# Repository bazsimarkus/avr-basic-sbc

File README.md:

<h1 align="center">avr-basic-sbc</h1>

<p align="center">
  <strong>An ATmega1284P-based single board computer</strong><br>
  Composite video output &bull; PS/2 keyboard input &bull; Tiny BASIC interpreter with graphics, sound, GPIO, and serial I/O
</p>

<p align="center">
  <table align="center">
    <tr>
      <td align="center">
        
      </td>
      <td align="center">
        
      </td>
    </tr>
  </table>
</p>

---

## Table of Contents

- [Overview](#overview)
- [Features](#features)
- [Hardware](#hardware)
  - [Main Board](#main-board)
  - [Schematic](#schematic)
  - [Bill of Materials](#bill-of-materials)
  - [Pin Mapping](#pin-mapping)
- [Firmware](#firmware)
  - [Architecture](#architecture)
  - [Graphics & Video](#graphics--video)
  - [Tiny BASIC Interpreter](#tiny-basic-interpreter)
  - [Building & Flashing](#building--flashing)
- [Boomerang Shields](#boomerang-shields)
  - [Serial Boomerang Shield](#serial-boomerang-shield)
  - [Bluetooth Boomerang Shield](#bluetooth-boomerang-shield-perfboard-prototype)
  - [Seven Segment Display Extension](#seven-segment-display-extension-perfboard-prototype)
- [SBC Studio](#sbc-studio)
  - [Code Editor & Serial Upload](#code-editor--serial-upload)
  - [Bitmap Editor & Loader](#bitmap-editor--loader)
  - [MIDI to BAS Converter](#midi-to-bas-converter)
- [BASIC Examples](#basic-examples)
  - [Hello World](#hello-world)
  - [Graphics Demos](#graphics-demos)
  - [Games](#games)
  - [Sound Examples](#sound-examples)
  - [Hardware I/O Examples](#hardware-io-examples)
- [Known Limitations & Future Ideas](#known-limitations--future-ideas)
- [Personal Notes](#personal-notes)
- [Inspirations & Credits](#inspirations--credits)

---

## Overview

I always loved retrocomputing. As a kid I played around with a Commodore 64 - which I still own to this day - and I was always fascinated by the fact that computers are really just embedded systems, just nowadays unimaginably fast ones. This project grew out of that fascination.

The idea is not completely original. Many people have built similar things, and my two biggest inspirations were Jörg Wolfram's [AVR ChipBASIC](https://www.jcwolfram.de/projekte/avr/chipbasic/main.php) and Juan J. Martínez's [DAN64](https://www.usebox.net/jjm/dan64/). Neither was quite what I had in mind though - I wanted something simple to use, simple to develop for, and simple to build. A Tiny BASIC based single board computer with composite video output, a PS/2 keyboard, and some GPIO, all on a single through-hole PCB. So I decided to build my own, and here it is.

The **AVR-SBC** is an ATmega1284P-based single board computer running a Tiny BASIC interpreter. It generates a composite video signal (320×240, PAL) directly from the microcontroller, accepts input from a PS/2 keyboard, has an onboard buzzer for sound, and exposes GPIO pins for interacting with the outside world. There is also an external 25LC640 SPI EEPROM for storing programs and data - I particularly like using it to store bitmaps that can be drawn on the screen. The internal EEPROM of the ATmega1284P is available too, so a typical setup is storing a drawing program in the internal EEPROM and the actual bitmap data in the external one.

The whole thing is built with plain `avr-gcc` and `avrdude`. No Arduino framework, no dependencies - just good old C and a bit of assembly where the timing gets tight.

---

## Features

- **ATmega1284P** running at 16 MHz - 128 KB flash, 16 KB SRAM, 4 KB internal EEPROM
- **Composite video output** via RCA jack - 320×240 PAL, generated directly by the MCU
- **PS/2 keyboard input** - supports EN (QWERTY), DE (QWERTZ), and HU (QWERTZ) layouts, selectable at compile time
- **Tiny BASIC interpreter** - interactive prompt with 40×30 character terminal, blinking cursor, and a nice MS-DOS style 8×8 font
- **Graphics library** - pixel, line, rectangle, filled rectangle, circle, filled circle, ellipse, triangle, bitmap drawing, and more
- **Onboard piezo buzzer** - `TONE`, `TONEW`, `NOTONE` commands for playing melodies, with a slide switch to disable it
- **External 25LC640 SPI EEPROM** (8 KB) - accessible from BASIC via `XPOKE`, `XPEEK`, `XSAVE`, `XLOAD`, `XFORMAT`; great for storing bitmaps
- **Internal EEPROM** (4 KB) - accessible via `EPOKE`, `EPEEK`, `ESAVE`, `ELOAD`, `EFORMAT`
- **GPIO** - `DWRITE`, `DREAD`, `AWRITE`, `AREAD` commands using MightyCore-style pin numbering
- **UART1 serial interface** - for uploading programs from a PC via `SERLOAD`
- **Two onboard LEDs** - red power indicator, yellow user-controllable LED on PD6
- **Tactile reset button** and **power toggle switch**
- **5V regulated power** via L7805CV from a standard DC barrel jack
- **No Arduino framework** - built entirely with `avr-gcc` and `avrdude`
- **Boomerang shields** - stackable expansion boards for serial USB and Bluetooth program upload *(see [Boomerang Shields](#boomerang-shields))*
- **SBC Studio** - companion Python app for editing, uploading, bitmap conversion, and MIDI-to-BASIC conversion *(see [SBC Studio](#sbc-studio))*

---

## Hardware

### Main Board

The AVR-SBC is a fully through-hole PCB, which was a deliberate choice - it makes it easy to solder by hand and easy to modify. The board is revision **v1.2**. Versions v1.0 and v1.1 were non-working prototypes that got soldered, debugged, and eventually thrown away. The third one worked, and it has been working reliably ever since.

The heart of the board is the **ATmega1284P** in a DIP-40 socket, running off a 16 MHz HC49-U crystal. Power comes in through a standard 2.1mm DC barrel jack and is regulated to 5V by an **L7805CV** linear regulator. There are two LEDs - a red power indicator and a yellow user-controllable one on PD6. A tactile button handles reset, a toggle switch controls power, and a slide switch can disconnect the buzzer if you get tired of the beeping.

Video goes out through an RCA jack. The PS/2 keyboard connector is a right-angle Mini-DIN. There is also an external **25LC640** SPI EEPROM in a DIP-8 socket, and a 2×5 USBasp ISP programming header.

---

### Schematic

The full KiCad project including schematic, PCB, and Gerber files is available in the `schematic/` folder.

---

### Bill of Materials

| Reference | Qty | Value / Part |
|-----------|-----|--------------|
| U1 | 1 | ATmega1284P-P (DIP-40) |
| U2 | 1 | L7805CV - 5V linear regulator (TO-220) |
| U3 | 1 | 25LC640 - SPI EEPROM 8KB (DIP-8) |
| Y1 | 1 | 16 MHz crystal (HC49-U) |
| BZ1 | 1 | Buzzer (polarized, 1201 footprint) |
| C1, C2 | 2 | 22 pF - crystal load capacitors |
| C3 | 1 | 3.3 µF electrolytic |
| C4 | 1 | 1 µF electrolytic |
| C5 | 1 | 4.7 µF electrolytic |
| D1 | 1 | LED 5mm RED - power indicator |
| D2 | 1 | LED 5mm YELLOW - user LED (PD6) |
| R1, R5, R6 | 3 | 10 kΩ |
| R2, R3, R7, R8 | 4 | 470 Ω |
| R4 | 1 | 1 kΩ |
| S1 | 1 | Tactile button 6×6mm - reset |
| S2 | 1 | Toggle switch 7×7mm - power |
| S3 | 1 | Slide switch - buzzer on/off |
| J1 | 1 | DC barrel jack 2.1mm (DC-005) |
| J2 | 1 | PS/2 keyboard connector (Mini-DIN 6) |
| J3 | 1 | RCA video jack |
| J4-J7 | 4 | Pin headers - Port B, A, C, D GPIO |
| J8 | 1 | 2×5 pin header - USBasp ISP |
| J9 | 1 | 2×4 pin header - power output |

---

### Pin Mapping

The firmware uses **MightyCore-style** pin numbering for the ATmega1284P, which is also what the BASIC `DWRITE`, `DREAD`, `AWRITE`, and `AREAD` commands expect.

| Pin | Port | Function | Available? |
|-----|------|----------|------------|
| 0 | PB0 | PS/2 keyboard clock | ✗ reserved |
| 1-3 | PB1-PB3 | GPIO (J4) | ✓ |
| 4-7 | PB4-PB7 | SPI - EEPROM /CS, MOSI, MISO, SCK | shared |
| 8 | PD0 | PS/2 keyboard data | ✗ reserved |
| 9 | PD1 | UART1 TX | ✓ |
| 10 | PD2 | UART1 RX | ✓ |
| 11-12 | PD3-PD4 | GPIO (J7) | ✓ |
| 13 | PD5 | Video sync output | ✗ reserved |
| 14 | PD6 | Yellow LED | ✓ |
| 15 | PD7 | Buzzer / OC2A | ✓ |
| 16-23 | PC0-PC7 | GPIO (J6) - fully free | ✓ |
| 24-30 | PA0-PA6 | GPIO (J5) - exposed on header, but see note | ⚠ see note |
| 31 | PA7 | Video data output | ✗ reserved |

> **Note on PORTA:** The high-resolution line rendering routine writes pixel data to the entire PORTA register using the AVR `OUT` instruction (1 cycle, cycle-exact timing). This means the whole port is effectively owned by the video system at runtime. The pins are physically accessible on the J5 header, but using them as GPIO will corrupt the video output. PORTC is the recommended alternative for free GPIO pins.

---

## Firmware

### Architecture

The firmware is pure C (and one assembly file), built with `avr-gcc` and flashed with `avrdude`. No Arduino framework, no HAL, no magic. Everything is wired up by hand.

The three hardware timers are each assigned a dedicated role and they all have to coexist without stepping on each other, which was honestly one of the trickier parts of getting this running:

| Timer | Role |
|-------|------|
| Timer0 | 1 ms system tick (CTC mode) - used by `DELAY` and the tone duration counter |
| Timer1 | Composite video sync and scanline generation |
| Timer2 | Tone output on OC2A / PD7 - drives the buzzer via `TONE` / `TONEW` |

Memory is tight. The ATmega1284P has 16 KB of SRAM, and between the 9600-byte framebuffer (320×240 ÷ 8) and the 5500-byte BASIC program buffer, there is not much room left. It works, but there is not a lot of headroom to play with.

---

### Graphics & Video

The video output is the part I am most proud of - and the part that gave me the most trouble.

I originally used the Arduino TVout library like most similar projects do. It works, but the resolution is limited and I never really liked how it looked. I wanted 320×240, so I decided to write my own graphics library. That turned out to be a good decision, but it had consequences.

The line rendering function - `render_scanline()` in `render_line.S` - has to output one pixel every single clock cycle to hit 320 pixels per line at 16 MHz. There is simply no way to do that in C. Even a tight loop has overhead that breaks the timing. So I wrote it in AVR assembly, fully unrolled, 40 bytes × 8 bits per byte, outputting each pixel with a single `OUT` instruction directly to PORTA. No loop, no branches, just 320 consecutive `OUT` and `LSL` pairs.

The downside is that `OUT` writes to the entire port at once. That means **PORTA is permanently reserved** by the video system at runtime - the pins are physically on the J5 header, but you cannot use them as GPIO without corrupting the video output. PORTC has 8 fully free pins (J6) and is the recommended alternative. I never found a way around this limitation at 320×240, so I left it as-is. Ideas are welcome.

The graphics library (`graphics.c`) supports:

- Pixels, lines (Bresenham), horizontal and vertical lines
- Rectangles, filled rectangles, rounded rectangles
- Circles, filled circles, ellipses, filled ellipses
- Triangles, filled triangles
- Bitmap drawing from RAM or PROGMEM
- 8×8 font character rendering (MS-DOS style)
- Three draw modes: `SET`, `CLEAR`, `XOR`

The text terminal layer (`text.c`) sits on top of the graphics library and provides a 40×30 character terminal with scrolling, wrap-around, and a blinking cursor.

---

### Tiny BASIC Interpreter

The firmware is almost a direct port of **TinyBASIC**, originally written by Gordon Brandly as *68000 Tiny Basic*, then ported to C by Michael Field as *Arduino Basic*, and further developed by Scott Lawrence as *TinyBasicPlus*. I adapted it to be fully AVR C based - no Arduino framework anywhere.

On startup, the board displays a splash screen with the firmware version and available memory, then drops into the interactive `>` prompt.

The BASIC command set includes everything you would expect, plus a bunch of hardware-specific extensions:

#### Core Commands

| Command | Description | Example |
|---------|-------------|---------|
| `PRINT expr, expr, ...` | Prints expressions (strings or numbers) to the screen. Items separated by `,`. End with `;` to suppress newline. `?` is a shorthand alias. | `PRINT "HELLO", X` |
| `INPUT var` | Prompts the user with `?` and reads a numeric value into variable `var` (A-Z). | `INPUT A` |
| `LET var = expr` | Assigns the value of an expression to a variable (A-Z). The `LET` keyword is optional. | `LET X = 42` or `X = 42` |
| `IF expr THEN statement` | Evaluates expression; if non-zero, executes the statement after `THEN`. `THEN` is optional. Relational operators: `=`, `<>`, `!=`, `<`, `>`, `<=`, `>=`. | `IF X > 10 THEN PRINT "BIG"` |
| `GOTO expr` | Jumps to the line number given by the expression. | `GOTO 100` |
| `GOSUB expr` | Calls the subroutine at the given line number, pushing a return address onto the stack. | `GOSUB 500` |
| `RETURN` | Returns from the most recent `GOSUB` call. | `RETURN` |
| `FOR var = expr TO expr [STEP expr]` | Begins a counting loop. Variable iterates from start to end value. `STEP` defaults to 1 if omitted. | `FOR I = 1 TO 10 STEP 2` |
| `NEXT var` | Advances the `FOR` loop variable and branches back if the loop has not finished. | `NEXT I` |
| `END` | Stops program execution and returns to the prompt. | `END` |
| `STOP` | Same as `END` - stops program execution. | `STOP` |
| `REM text` | Comment line; everything after `REM` (or `'`) is ignored. | `REM THIS IS A COMMENT` |

#### Program Management

| Command | Description | Example |
|---------|-------------|---------|
| `RUN` | Executes the stored program from the first line. | `RUN` |
| `LIST [linenum]` | Lists the stored program. If a line number is given, listing starts from that line. | `LIST` or `LIST 100` |
| `NEW` | Erases the stored program from memory. | `NEW` |
| `LOAD` | Loads a program (stub - unimplemented on this platform). | `LOAD` |
| `SAVE` | Saves a program (stub - unimplemented on this platform). | `SAVE` |
| `CHAIN` | Loads a program and auto-runs it after loading (stub - unimplemented on this platform). | `CHAIN` |
| `MEM` | Prints the number of free BASIC program bytes and EEPROM usage statistics. | `MEM` |
| `BYE` | Exits the BASIC interpreter. | `BYE` |

#### GPIO

| Command | Description | Example |
|---------|-------------|---------|
| `DWRITE pin, value` | Sets a digital GPIO pin HIGH or LOW. Value can be `HIGH`/`HI`, `LOW`/`LO`, or a numeric expression (0/1). Uses MightyCore pin numbering. | `DWRITE 14, 1` |
| `AWRITE pin, value` | Writes an analog (PWM) value to a GPIO pin. Same syntax as `DWRITE`. | `AWRITE 14, 128` |
| `DREAD(pin)` | Function - reads a digital pin and returns 1 (HIGH) or 0 (LOW). Enables the internal pull-up resistor. | `X = DREAD(16)` |
| `AREAD(pin)` | Function - reads an analog value (0-1023) from an ADC pin (pins 24-30 only). | `X = AREAD(24)` |

#### Graphics

| Command | Description | Example |
|---------|-------------|---------|
| `DRAWPIX x, y, c` | Draws a single pixel at (x, y) with draw mode `c` (0=clear, 1=set, 2=xor). | `DRAWPIX 160, 120, 1` |
| `DRAWLINE x0, y0, x1, y1, c` | Draws a line from (x0, y0) to (x1, y1) with draw mode `c`. | `DRAWLINE 0, 0, 319, 239, 1` |
| `DRAWRECT x, y, w, h, c, f` | Draws a rectangle at (x, y) with width `w` and height `h`. Outline uses draw mode `c`, fill uses draw mode `f`. Use -1 for `f` to draw outline only. | `DRAWRECT 10, 10, 50, 30, 1, 1` |
| `DRAWCIRC cx, cy, r, c, f` | Draws a circle centered at (cx, cy) with radius `r`. Outline uses draw mode `c`, fill uses draw mode `f`. Use -1 for `f` to draw outline only. | `DRAWCIRC 160, 120, 40, 1, 0` |
| `DRAWCHAR x, y, char` | Draws a single 8×8 character at pixel position (x, y). The character is the literal next character in the source. | `DRAWCHAR 10, 10, A` |
| `GETPIX x, y` | Prints the pixel value (0 or 1) at position (x, y) to the screen. | `GETPIX 100, 50` |
| `CLS` | Clears the entire screen and resets the text cursor. | `CLS` |

#### Sound

| Command | Description | Example |
|---------|-------------|---------|
| `TONE freq, duration` | Starts playing a tone at `freq` Hz for `duration` ms on the buzzer. Execution continues immediately. | `TONE 440, 500` |
| `TONEW freq, duration` | Plays a tone at `freq` Hz for `duration` ms and **waits** until the tone finishes before continuing. | `TONEW 440, 500` |
| `NOTONE` | Immediately stops any tone currently playing. | `NOTONE` |

#### Timing

| Command | Description | Example |
|---------|-------------|---------|
| `DELAY expr` | Pauses execution for the given number of milliseconds. Breakable with ESC or Ctrl-C. | `DELAY 1000` |

#### Internal EEPROM (4 KB)

| Command | Description | Example |
|---------|-------------|---------|
| `ESAVE` | Saves the current program to internal EEPROM. | `ESAVE` |
| `ELOAD` | Loads a program from internal EEPROM into RAM. | `ELOAD` |
| `ELIST` | Lists the contents of the internal EEPROM to the screen. | `ELIST` |
| `EFORMAT` | Erases the entire internal EEPROM (fills with zeros). | `EFORMAT` |
| `EPOKE value, addr` | Writes `value` (byte) to internal EEPROM at address `addr`. | `EPOKE 65, 0` |
| `EPEEK var, addr` | Reads a byte from internal EEPROM at address `addr` into variable `var` (A-Z). | `EPEEK A, 0` |

#### External EEPROM (8 KB - 25LC640)

| Command | Description | Example |
|---------|-------------|---------|
| `XSAVE` | Saves the current program to external SPI EEPROM. | `XSAVE` |
| `XLOAD` | Loads a program from external EEPROM into RAM. | `XLOAD` |
| `XLIST` | Lists the contents of the external EEPROM to the screen. | `XLIST` |
| `XFORMAT` | Erases the entire external EEPROM (fills with zeros). | `XFORMAT` |
| `XPOKE value, addr` | Writes `value` (byte) to external EEPROM at address `addr`. | `XPOKE 65, 0` |
| `XPEEK var, addr` | Reads a byte from external EEPROM at address `addr` into variable `var` (A-Z). | `XPEEK A, 0` |

#### Serial (UART1)

| Command | Description | Example |
|---------|-------------|---------|
| `SEROPEN` | Opens UART1 at 9600 baud for serial communication. | `SEROPEN` |
| `SERCLOSE` | Closes UART1. | `SERCLOSE` |
| `SERPRINT expr, expr, ...` | Sends expressions (strings or numbers) over UART1. Same syntax as `PRINT`. | `SERPRINT "HELLO"` |
| `SERREAD` | Reads and displays characters from UART1 until a newline or 5-second timeout. | `SERREAD` |
| `SERLOAD` | Loads a BASIC program from UART1 into RAM (used for PC upload via SBC Studio). | `SERLOAD` |

#### Miscellaneous

| Command | Description | Example |
|---------|-------------|---------|
| `INKEY var` | Non-blocking keyboard read. Stores the ASCII value of the pressed key into variable `var` (A-Z), or 0 if no key is pressed. | `INKEY K` |
| `RSEED expr` | Seeds the random number generator with the given value. | `RSEED 42` |
| `POKE addr, value` | Writes `value` (byte) to RAM address `addr` within the BASIC memory buffer. | `POKE 0, 65` |
| `PEEK(addr)` | Function - reads a byte from RAM address `addr` within the BASIC memory buffer. | `X = PEEK(0)` |
| `ABS(expr)` | Function - returns the absolute value of the expression. | `X = ABS(-5)` |
| `RND(expr)` | Function - returns a random integer from 0 to `expr`-1. | `X = RND(100)` |

#### Operators

| Operator | Description |
|----------|-------------|
| `+`, `-`, `*`, `/` | Arithmetic: addition, subtraction, multiplication, integer division |
| `=`, `<>`, `!=`, `<`, `>`, `<=`, `>=` | Relational operators (return 1 if true, 0 if false) |
| `-expr` | Unary negation |
| `(expr)` | Parentheses for grouping |

#### Notes:

- Line numbers are required for stored programs (e.g. `10`, `20`, `30`). Direct commands can be typed without a line number.
- Variables: single uppercase letters `A`-`Z`, 16-bit signed integers (-32768 to 32767)
- Strings in double or single quotes: `"HELLO"` or `'HELLO'`
- Multiple statements per line separated by `:` - e.g. `10 A=1 : B=2 : PRINT A+B`
- Screen resolution: 320×240 pixels (x: 0-319, y: 0-239)
- Program RAM: 5500 bytes total
- Break execution at any time with **ESC** or **Ctrl-C**

---

### Building & Flashing

**Requirements:** `avr-gcc`, `avr-libc`, `avrdude`, and `make`. On Windows, [WinAVR](https://winavr.sourceforge.net/) or Microchip Studio works fine. On Linux/macOS, install from your package manager.

```bash
# Build with default US/English keyboard layout
make

# Build with German QWERTZ layout
make KB_LAYOUT=DE

# Build with Hungarian QWERTZ layout
make KB_LAYOUT=HU

# Flash via USBasp programmer
make flash

# Show flash / SRAM / EEPROM usage
make size
```

The Makefile also exposes feature flags if you want to disable subsystems:

```bash
# Build without tone support (frees Timer2)
make FEAT_TONES=0

# Build without external EEPROM support
make FEAT_XEEPROM=0
```

**Flashing** is done via the 2×5 USBasp ISP header (J8). One important thing to be aware of: **the 5V pin on the ISP header is not connected**. The board must be powered through the DC barrel jack before you can flash it. This was a conscious decision on v1.2 to avoid back-feeding the microcontroller through the programmer.

The default programmer in the Makefile is `usbasp`. If you use something else, change the `-c usbasp` flag in the `flash` target accordingly.

---

## Boomerang Shields

After a while, connecting an FTDI USB-serial cable to PD2 and PD3 every time I wanted to upload a program got old really fast. So I opened KiCad again and designed a small stackable expansion board - the **Boomerang Shield**.

Why boomerang? Because of the shape. It has cutouts for the crystal and capacitors, and it follows the contour of the pin headers on the main board. I didn't mean for it to look like a boomerang, it just happened that way. I didn't want to redesign it - this is already the third revision of the main board - so the name stuck.

The shields use the same 2.54mm pin headers as the main board and stack directly on top. Pin headers are also broken out on the shield itself so GPIO access is not lost.

---

### Serial Boomerang Shield

The serial boomerang shield is the official one. It carries a **CP2102 USB-to-serial bridge module**, connects to UART1 (PD2/PD3) of the AVR-SBC, and exposes a micro-USB connector. That's it - but now I can just leave it sitting on top of the board and upload programs with a single cable. Much better.

The KiCad project, schematic, and Gerber files for the serial boomerang shield are in the `boomerang-shields/serial-boomerang-shield/` folder. There is also an **empty boomerang shield template** in `boomerang-shields/empty-boomerang-shield-template/` if you want to design your own expansion.

---

### Bluetooth Boomerang Shield *(perfboard prototype)*

Once I had the serial shield working, I started thinking about what else could plug into the same spot. The CP2102 module and an **HC-06 Bluetooth Classic module** have a very similar pinout - both are essentially a UART bridge. So I quickly wired one up on a perfboard with the same pin header footprint as the serial shield, plugged it in, and it worked.

When the HC-06 is paired with a PC, it shows up as a virtual COM port via Bluetooth Classic SPP - exactly the same as the USB cable. That means I can upload BASIC programs to the AVR-SBC completely wirelessly. Which is, honestly, pretty amazing for a board built around an 8-bit microcontroller.

There is no official PCB design for the Bluetooth boomerang yet - it lives on a perfboard prototype for now. If I ever design it properly, I would probably use a better module, something like a Würth Elektronik Proteus-IV, a Skoll-I, or an ESP32-based module.

---

### Seven Segment Display Extension *(perfboard prototype)*

I also soldered together a small perfboard circuit with a **seven segment display** that stacks on top of the boomerang shield.

So at one point I had three layers: AVR-SBC → Serial Boomerang Shield → Seven Segment Extension. There is a BASIC example for it in the `examples/` folder.

Like the Bluetooth shield, this one never got an official PCB design. It remains a perfboard prototype.

---

## SBC Studio

SBC Studio is a companion Python application for the AVR-SBC. It started as a simple serial uploader - basically just a way to type programs into the board really fast over UART1 without having to sit at a PS/2 keyboard. Over time it grew into something more, so I gave it a proper name.

It requires Python 3 with `pyserial`. The bitmap tools also need `Pillow`, and the MIDI converter needs `pretty_midi`. Everything else is standard library.

```bash
pip install pyserial Pillow pretty_midi
python sbc-studio.py
```

The source is in `pc-tools/sbc-studio/`.

---

### Code Editor & Serial Upload

The main window is a lightweight `.bas` file editor with syntax highlighting, line numbers, tab support, find & replace, and undo/redo. It is nothing fancy, but it is comfortable enough for writing and editing Tiny BASIC programs.

The serial upload works by opening UART1 at 9600 baud and sending the program character by character - essentially simulating someone typing it in at the `>` prompt, just very fast. To upload, select your COM port from the toolbar, open or write a `.bas` file, and hit upload. The board receives it line by line exactly as if you had typed it yourself.

The keyboard layout for the PS/2 side (EN/DE/HU) is selected at firmware compile time, but the upload always goes through serial so the layout doesn't matter there.

---

### Bitmap Editor & Loader

This was a fun one to build. The **Bitmap Editor** takes any image file and converts it to a 128×64 monochrome bitmap suitable for the AVR-SBC screen. It has options for scaling, centering, dithering (Floyd-Steinberg), threshold control, rotation, flip, and background colour. The output is a standard 1-bit `.bmp` file.

The **Bitmap Loader** then uploads that `.bmp` to the AVR-SBC's external 25LC640 EEPROM via serial, using `XPOKE` commands split into batches. Once uploaded, a small BASIC program reads the bitmap back out with `XPEEK` and draws it pixel by pixel with `DRAWPIX`.

I included two examples in `pc-tools/sbc-studio/sbc-studio-output/bitmap-editor/` - a photo of our dog and a flower.

The reason I like this so much is that the external EEPROM fits a 128×64 bitmap very comfortably, and you never have to take the chip out of the socket to reprogram it. Everything goes over serial.

---

### MIDI to BAS Converter

At some point I realised that the `TONEW` command - which plays a tone at a given frequency and waits for it to finish - maps almost perfectly onto MIDI note data. So I built a converter that takes a single-track `.mid` file, extracts the notes, calculates frequencies and durations, and outputs a `.bas` file full of `TONEW` and `DELAY` statements that the AVR-SBC can play on its onboard buzzer.

The output is capped at around 5300 bytes to fit the BASIC program buffer. It is not going to replace a proper audio system, but hearing Für Elise come out of a piezo buzzer on a board you built yourself is genuinely satisfying. Two examples are included in `pc-tools/sbc-studio/sbc-studio-output/midi-to-bas-converter/` - Für Elise and Ode to Joy.

---

## BASIC Examples

Once the board was up and running I could finally sit down and actually write some programs for it in Tiny BASIC. The examples are all in the `examples/` folder. They cover a bit of everything - games, graphics demos, sound, and hardware I/O.

All of them can be typed in at the `>` prompt directly, or uploaded from a PC using SBC Studio.

---

### Hello World

The simplest possible start. The `PRINT` command outputs text to the screen.

```basic
PRINT "HELLO"
```

---

### Graphics Demos

The graphics library makes it easy to draw shapes directly from BASIC. These examples show off what the 320×240 display can do.

| File | Description |
|------|-------------|
| `ConcentricCircles.bas` | Draws concentric circles filling the screen |
| `RandomRectangles.bas` | Fills the screen with randomly placed rectangles |
| `Spirograph.bas` | Spirograph-style pattern using lines and loops |
| `StarField.bas` | Scrolling star field effect |
| `BouncingBall.bas` | A ball bouncing around the screen |

---

### Games

A few simple games that show off keyboard input, random numbers, and the graphics commands together.

| File | Description |
|------|-------------|
| `EatTheTargets.bas` | Move a cursor around the screen and eat targets |
| `GuessTheNumber.bas` | Classic guess the number game with hints |
| `SlotMachine.bas` | An ASCII slot machine |

---

### Sound Examples

These use the `TONE` and `TONEW` commands to play melodies on the onboard buzzer. The MIDI converter in SBC Studio was used to generate the two classical pieces.

| File | Description |
|------|-------------|
| `CMajorPiano.bas` | Plays a C major scale using the keyboard |
| `MelodyPlayer.bas` | A simple melody player |
| `furelise.bas` *(generated)* | Für Elise - in `pc-tools/sbc-studio/sbc-studio-output/midi-to-bas-converter/` |
| `odetojoy.bas` *(generated)* | Ode to Joy - in `pc-tools/sbc-studio/sbc-studio-output/midi-to-bas-converter/` |

---

### Hardware I/O Examples

These examples interact with the GPIO pins and show how `DWRITE`, `DREAD`, and the EEPROM commands work in practice.

| File | Description |
|------|-------------|
| `BlinkLED.bas` | Blinks the onboard yellow LED on PD6 using `DWRITE` |
| `SevenSegmentDisplay.bas` | Drives a seven segment display connected to PORTC |

---

## Known Limitations & Future Ideas

The board works, and it works reliably. But it is not perfect, and I know exactly where the rough edges are.

---

### Hardware

**Decoupling capacitors** - when I designed the board I was quite casual with component choices, and I skipped the per-chip decoupling capacitors. There are bulk capacitors for the microcontroller and the L7805CV, but they are not following the reference design. If I were to redesign the board I would definitely add proper decoupling caps on every supply pin.

**No reverse polarity protection** - the DC input has no protection diode. Plugging in the barrel jack the wrong way around will likely kill the board. A simple series diode or a P-channel MOSFET would fix this.

**No Schottky diode on the ISP header** - to prevent back-feeding the microcontroller through the programmer's VCC pin, I simply left the 5V pin on the ISP header unconnected. It works, but a proper Schottky diode would be a cleaner solution. As it stands, the board must always be powered through the DC barrel jack when programming.

**PORTA reserved by the video system** - as described in the Firmware section, the cycle-exact line rendering routine writes to the entire PORTA register using the AVR `OUT` instruction. This means PA0-PA6 cannot be used as GPIO without corrupting the video output, even though the pins are physically accessible on the J5 header. Getting 320×240 resolution with proper timing while also making PORTA available as GPIO is an unsolved problem for this project. If you have an idea, I would love to hear it.

---

### Software & Features

**Boomerang shields without official PCBs** - the Bluetooth boomerang and the seven segment extension board are both perfboard prototypes. They work great but there are no KiCad files for them. At some point I would like to design proper PCBs for both - and when I do, I would probably swap the HC-06 for something more modern, like a Würth Elektronik Proteus-IV, a Skoll-I, or an ESP32-based module.

**Single-track MIDI only** - the MIDI to BAS converter in SBC Studio only handles single-track MIDI files. Multi-track files are not supported, which rules out a lot of MIDI content. Since the buzzer is monophonic anyway this is not a huge loss, but smarter track selection would be a nice improvement.

**Auto-run from EEPROM** - the firmware supports an `ENABLE_EAUTORUN` flag that automatically runs the program stored in internal EEPROM on boot, without showing the `>` prompt first. This is disabled by default but could be useful for standalone appliance-style deployments.

---

## Personal Notes

I started this project many years ago, then stopped, then restarted, then had a long pause. Many versions of KiCad were released in the meantime. AI systems started developing and becoming more and more advanced. And this project was still just there, waiting on a shelf somewhere between the other unfinished things. But occasionally when I came back to it, it made me very happy and I found it genuinely challenging.

Before this project I was usually defaulting to just using the Arduino framework - like the TVout-based firmware also did, and like many similar projects still do. But during this project I realized that with the power of real C and assembly you can get much further. Writing the line renderer in assembly, getting the timing right across three timers, squeezing everything into 16 KB of SRAM - none of that would have happened if I had stayed in Arduino land. So it was definitely a nice learning experience about myself too. Now there is no going back. Even the simplest things I do in low level C, and I have become really interested in assembly as well.

I am glad I have this project. I can't wait to see what the future brings with it - I am sure it will be exciting. And knowing myself, I will probably abandon it for a while again, and then one day come back and find something new to add. The hardware stays the same.

---

## Inspirations & Credits

### Inspiration Projects

This project would not exist without these two:

- **Jörg Wolfram** - [AVR ChipBASIC](https://www.jcwolfram.de/projekte/avr/chipbasic/main.php)
  The project that first showed me this kind of thing was possible on an AVR microcontroller.

- **Juan J. Martínez** - [DAN64](https://www.usebox.net/jjm/dan64/)
  A beautifully executed AVR-based home computer that was a big influence on the direction of this project.

---

### Tiny BASIC Lineage

The firmware interpreter is based on a long chain of ports and adaptations:

- **Gordon Brandly** - original *68000 Tiny Basic*
- **Michael Field** - ported to C as *Arduino Basic*
- **Scott Lawrence** - extended and maintained as [TinyBasicPlus](https://github.com/BleuLlama/TinyBasicPlus)

The AVR-SBC version is a bare-metal port of TinyBasicPlus, adapted for the ATmega1284P with no Arduino framework and extended with graphics, sound, EEPROM, and serial commands.

---

### Tools & Libraries

- [avr-gcc](https://gcc.gnu.org/wiki/avr-gcc) & [avr-libc](https://avr-libc.nongnu.org/) - the toolchain
- [avrdude](https://github.com/avrdudes/avrdude) - flashing utility
- [KiCad](https://www.kicad.org/) - schematic and PCB design
- [Python](https://www.python.org/) / [pyserial](https://github.com/pyserial/pyserial) / [Pillow](https://python-pillow.org/) / [pretty_midi](https://github.com/craffel/pretty-midi) - SBC Studio dependencies

---

<p align="center">
  
  <br>
  <em>Built with ❤️ and an 8-bit microcontroller</em>
</p>

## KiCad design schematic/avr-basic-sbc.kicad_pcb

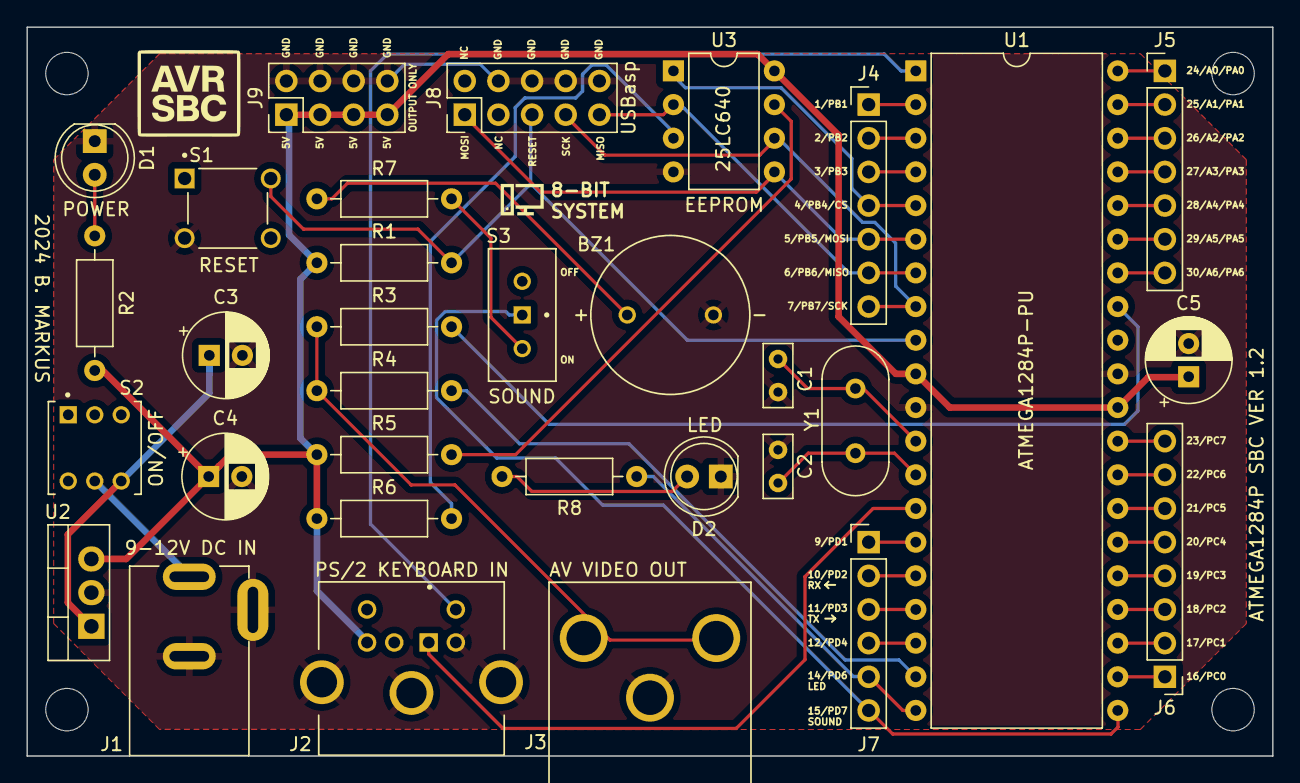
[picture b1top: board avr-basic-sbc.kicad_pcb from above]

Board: 2 copper layers, 94.0 x 55.0 mm, 38 parts (0 on the bottom side), 46 nets.

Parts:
BZ1: Buzzer 1201
C1, C2: 22pF; C_Rect_L4.6mm_W2.0mm_P2.50mm_MKS02_FKP02
C3: 0.33uF; CP_Radial_D6.3mm_P2.50mm
C4: 0.1uF; CP_Radial_D6.3mm_P2.50mm
C5: 4.7uF; CP_Radial_D6.3mm_P2.50mm
D1: LED 5mm RED; LED_D5.0mm_RED
D2: LED 5mm YELLOW; LED_D5.0mm_YELLOW
G2: LOGO
GRAPHICS2: LOGO
J1: DC-005 Power Jack
J2: PS/2 keyboard port; PS2-connector-keyboard
J3: RCA Video Jack
J4: Port B; PinHeader_1x07_P2.54mm_Vertical
J5: Port A; PinHeader_1x07_P2.54mm_Vertical
J6: Port C; PinHeader_1x08_P2.54mm_Vertical
J7: Port D; PinHeader_1x06_P2.54mm_Vertical
J8: USBasp header; PinHeader_2x05_P2.54mm_Vertical
J9: Power output header; PinHeader_2x04_P2.54mm_Vertical
MH1, MH2, MH3, MH4: MountingHole_3.2mm_M3_DIN965
R1, R5, R6: 10k; R_10k_Axial_DIN0207
R2, R3, R7, R8: 470R; R_470_Axial_DIN0207
R4: 1k; R_1k_Axial_DIN0207
S1: Button TACT 6x6mm
S2: Toggle Switch 7x7mm
S3: Slide Switch SS12D00
U1: ATmega1284P-P; DIP-40_W15.24mm
U2: L7805; TO-220-3_Vertical
U3: 25LC640; DIP-8_W7.62mm
Y1: 16 MHz; Crystal_HC49-U_Vertical

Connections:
+5V: C4.1, C5.1, J2.4, J9.1, J9.3, J9.5, J9.7, R1.1, R2.1, R5.1, R6.1, U1.10 (VCC), U1.30 (AVCC), U2.3 (OUT), U3.8 (VCC)
/POWER IN: J1.4, S2.5
/POWER IN 2: C3.1, S2.6, U2.1 (IN)
Clock: J2.5, U1.1 (PB0)
Data: J2.1, U1.14 (PD0)
GND: BZ1.2 (-), C1.2, C2.2, C3.2, C4.2, C5.2, D1.1 (K), D2.1 (K), J1.2, J1.3, J2.3, J2.S1, J2.S2, J2.S3, J3.1 (Shield), J8.4, J8.6, J8.8, J8.10, J9.2, J9.4, J9.6, J9.8, S1.3, U1.11 (GND), U1.31 (GND), U2.2 (GND), U3.4 (GND)
MISO: J4.6, J8.9, U1.7 (PB6), U3.2 (MISO)
MOSI: J4.5, J8.1, U1.6 (PB5), U3.5 (MOSI)
unnamed: BZ1.1 (+), R7.2
unnamed: D1.2 (A), R2.2
unnamed: D2.2 (A), R8.2
unnamed: J3.2 (Video), R3.1, R4.1
unnamed: J4.1, U1.2 (PB1)
unnamed: J4.2, U1.3 (PB2)
unnamed: J4.3, U1.4 (PB3)
unnamed: J5.1, U1.40 (PA0)
unnamed: J5.2, U1.39 (PA1)
unnamed: J5.3, U1.38 (PA2)
unnamed: J5.4, U1.37 (PA3)
unnamed: J5.5, U1.36 (PA4)
unnamed: J5.6, U1.35 (PA5)
unnamed: J5.7, U1.34 (PA6)
unnamed: J6.1, U1.22 (PC0)
unnamed: J6.2, U1.23 (PC1)
unnamed: J6.3, U1.24 (PC2)
unnamed: J6.4, U1.25 (PC3)
unnamed: J6.5, U1.26 (PC4)
unnamed: J6.6, U1.27 (PC5)
unnamed: J6.7, U1.28 (PC6)
unnamed: J6.8, U1.29 (PC7)
unnamed: J7.1, U1.15 (PD1)
unnamed: J7.2, U1.16 (PD2)
unnamed: J7.3, U1.17 (PD3)
unnamed: J7.4, U1.18 (PD4)
unnamed: J7.5, R8.1, U1.20 (PD6)
unnamed: J7.6, S3.1, U1.21 (PD7)
unnamed: R7.1, S3.2
unnamed: C2.1, U1.13 (XTAL1), Y1.2
unnamed: C1.1, U1.12 (XTAL2), Y1.1
unnamed: R5.2, U3.7 (~HOLD)
unnamed: R6.2, U3.3 (~WP)
RESET: J8.5, R1.2, S1.2, U1.9 (~RESET)
SCK: J4.7, J8.7, U1.8 (PB7), U3.6 (SCK)
Sync: R4.2, U1.19 (PD5)
Video: R3.2, U1.33 (PA7)
~CS: J4.4, U1.5 (PB4), U3.1 (~CS)

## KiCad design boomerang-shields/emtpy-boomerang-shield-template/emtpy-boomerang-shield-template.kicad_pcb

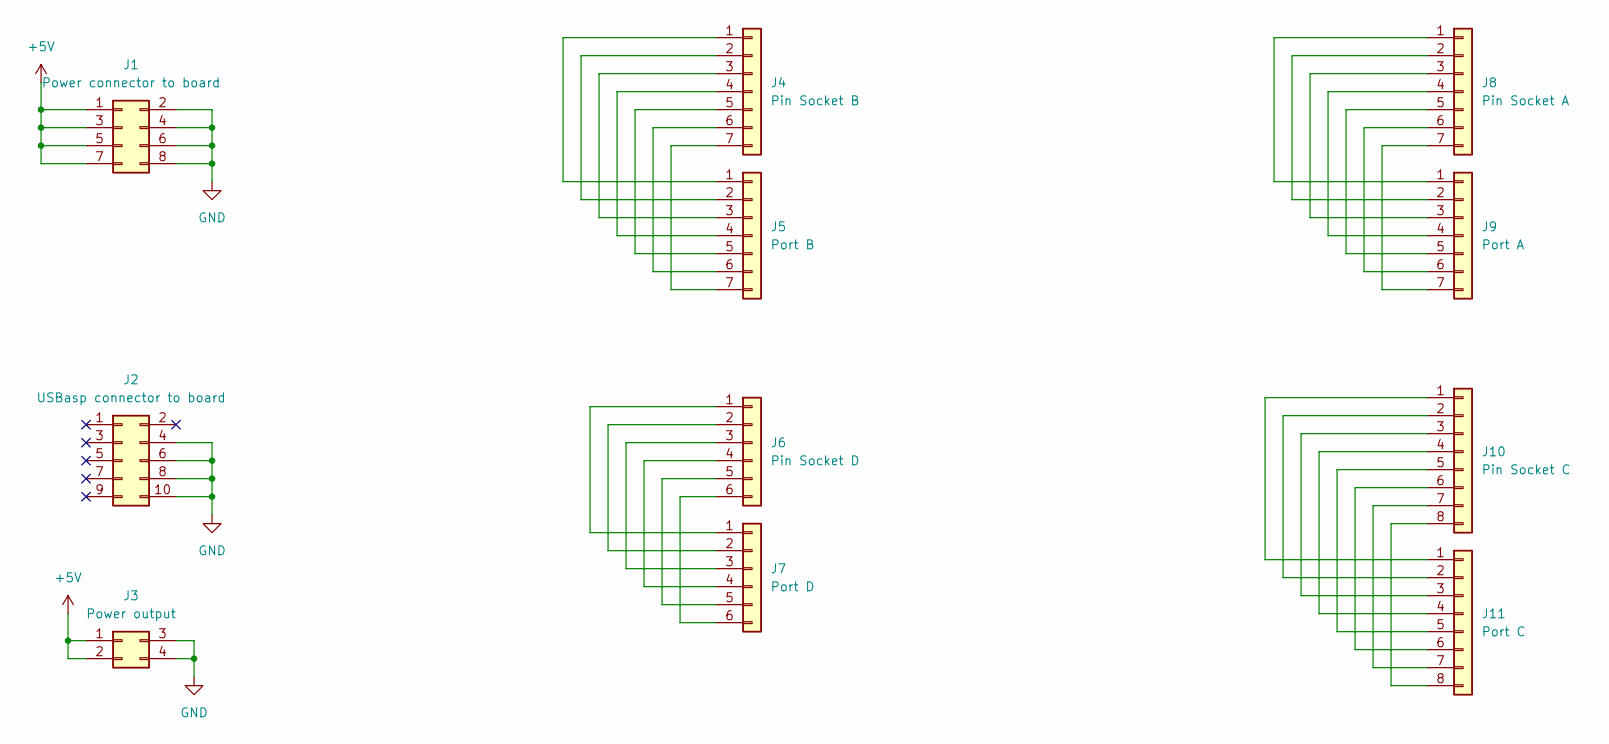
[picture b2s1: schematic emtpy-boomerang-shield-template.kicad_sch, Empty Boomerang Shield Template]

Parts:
J1: Power connector to board; PinHeader_2x04_P2.54mm_Vertical
J2: USBasp connector to board; PinHeader_2x05_P2.54mm_Vertical
J3: Power output; PinSocket_2x02_P2.54mm_Vertical
J4: Pin Socket B; PinSocket_1x07_P2.54mm_Vertical
J5: Port B; PinHeader_1x07_P2.54mm_Vertical
J6: Pin Socket D; PinSocket_1x06_P2.54mm_Vertical
J7: Port D; PinHeader_1x06_P2.54mm_Vertical
J8: Pin Socket A; PinSocket_1x07_P2.54mm_Vertical
J9: Port A; PinHeader_1x07_P2.54mm_Vertical
J10: Pin Socket C; PinSocket_1x08_P2.54mm_Vertical
J11: Port C; PinHeader_1x08_P2.54mm_Vertical

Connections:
+5V: J1.1, J1.3, J1.5, J1.7, J3.1, J3.2
GND: J1.2, J1.4, J1.6, J1.8, J2.4, J2.6, J2.8, J2.10, J3.3, J3.4
unnamed: J4.1, J5.1
unnamed: J4.2, J5.2
unnamed: J4.3, J5.3
unnamed: J4.4, J5.4
unnamed: J4.5, J5.5
unnamed: J4.6, J5.6
unnamed: J4.7, J5.7
unnamed: J6.1, J7.1
unnamed: J6.2, J7.2
unnamed: J6.3, J7.3
unnamed: J6.4, J7.4
unnamed: J6.5, J7.5
unnamed: J6.6, J7.6
unnamed: J8.1, J9.1
unnamed: J8.2, J9.2
unnamed: J8.3, J9.3
unnamed: J8.4, J9.4
unnamed: J8.5, J9.5
unnamed: J8.6, J9.6
unnamed: J8.7, J9.7
unnamed: J10.1, J11.1
unnamed: J10.2, J11.2
unnamed: J10.3, J11.3
unnamed: J10.4, J11.4
unnamed: J10.5, J11.5
unnamed: J10.6, J11.6
unnamed: J10.7, J11.7
unnamed: J10.8, J11.8

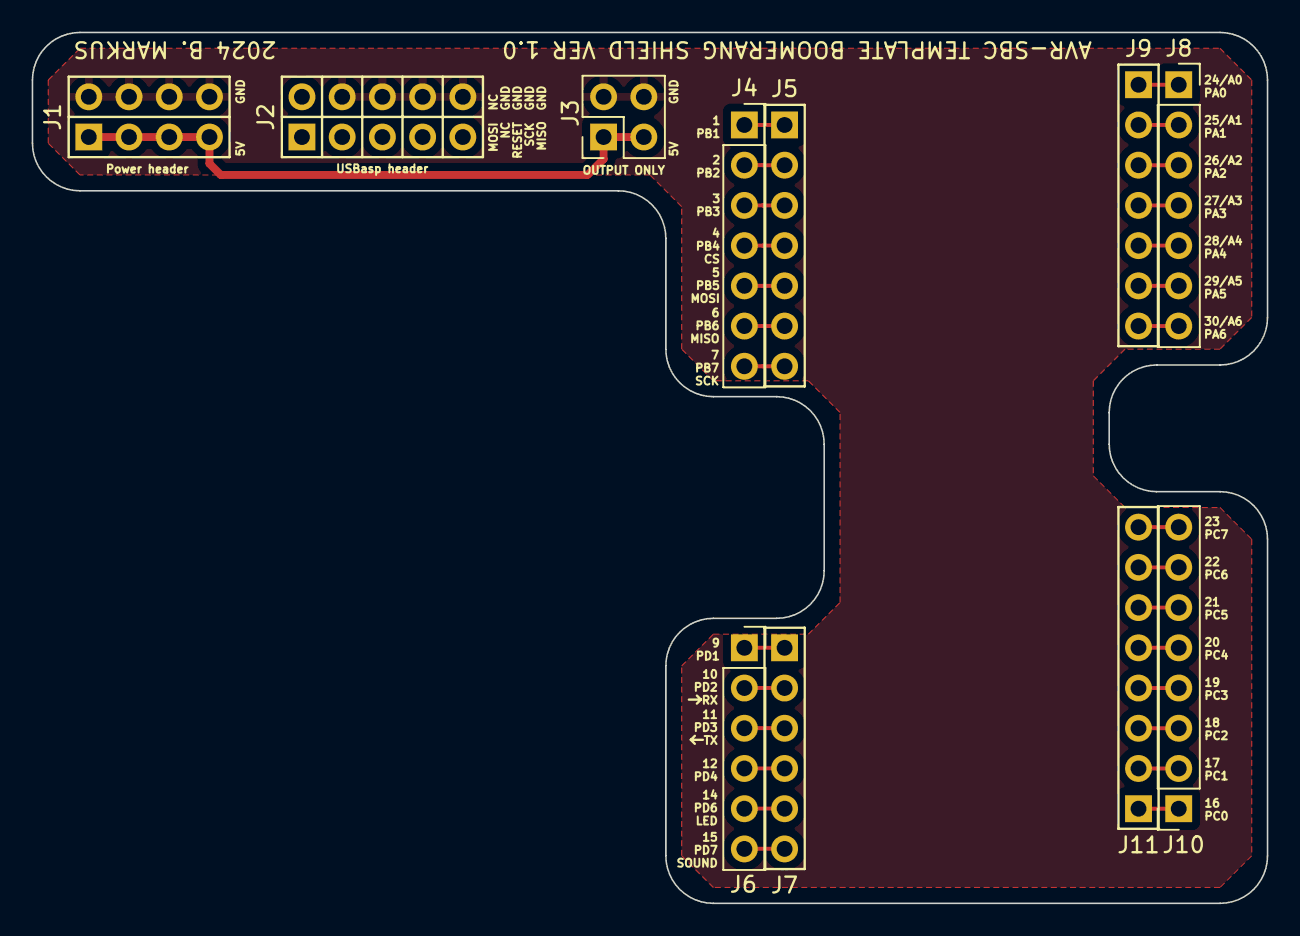
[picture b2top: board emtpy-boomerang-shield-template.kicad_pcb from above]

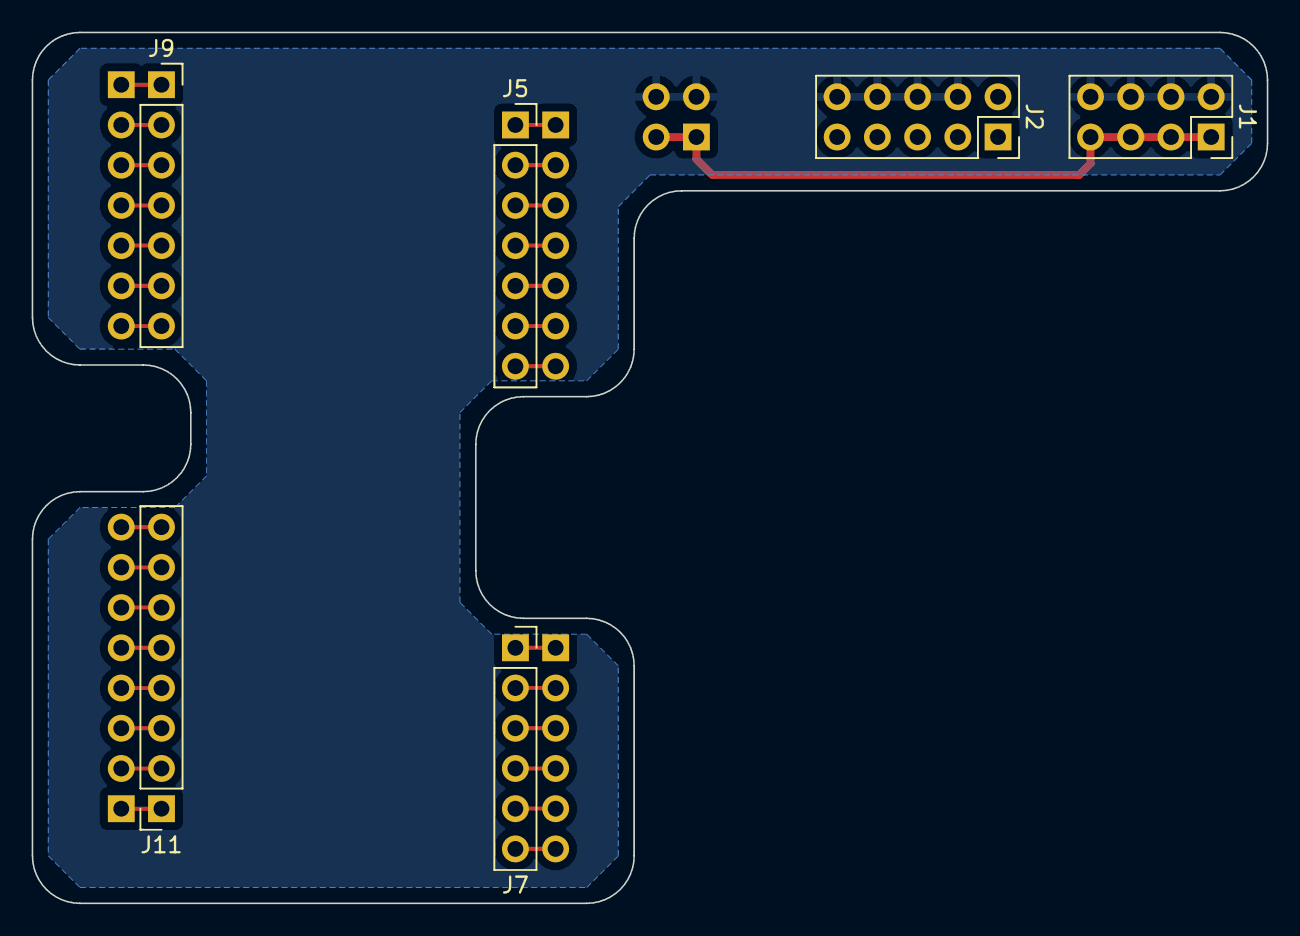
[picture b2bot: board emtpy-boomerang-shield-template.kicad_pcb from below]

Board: 2 copper layers, 78.0 x 55.0 mm, 11 parts (6 on the bottom side), 30 nets.

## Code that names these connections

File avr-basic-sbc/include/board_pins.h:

/*
 * board_pins.h  -  Hardware pin definitions for AVR-SBC v1.2
 *
 * Centralises all port/DDR/bit assignments so that changing the PCB layout
 * only requires editing this one file.  The BASIC interpreter accesses GPIO
 * through the AWRITE/DWRITE/AREAD/DREAD commands, which call the inline
 * helper functions defined at the bottom of this header.
 *
 * All assignments read directly from avr-basic-sbc.net (KiCad netlist).
 *
 * ============================================================
 * MightyCore Arduino-style pin number mapping
 * ============================================================
 *  Pin  Port/Bit  Notes
 *  ---  --------  -----------------------------------
 *   0   PB0       PS/2 keyboard clock  -- NOT AVAILABLE
 *   1   PB1       GPIO (J7)
 *   2   PB2       GPIO (J7)
 *   3   PB3       GPIO (J7)
 *   4   PB4       SPI /CS for EEPROM   -- shared with SPI
 *   5   PB5       SPI MOSI             -- shared with SPI
 *   6   PB6       SPI MISO             -- shared with SPI
 *   7   PB7       SPI SCK              -- shared with SPI
 *   8   PD0       PS/2 keyboard data   -- NOT AVAILABLE
 *   9   PD1       UART1 TX (J9)
 *  10   PD2       UART1 RX (J9)
 *  11   PD3       GPIO (J9)
 *  12   PD4       GPIO (J9)
 *  13   PD5       Video sync           -- NOT AVAILABLE
 *  14   PD6       Yellow LED (J9)
 *  15   PD7       Buzzer / OC2A
 *  16   PC0       GPIO (J8)
 *  17   PC1       GPIO (J8)
 *  18   PC2       GPIO (J8)
 *  19   PC3       GPIO (J8)
 *  20   PC4       GPIO (J8)
 *  21   PC5       GPIO (J8)
 *  22   PC6       GPIO (J8)
 *  23   PC7       GPIO (J8)
 *  24   PA0       GPIO (J6)
 *  25   PA1       GPIO (J6)
 *  26   PA2       GPIO (J6)
 *  27   PA3       GPIO (J6)
 *  28   PA4       GPIO (J6)
 *  29   PA5       GPIO (J6)
 *  30   PA6       GPIO (J6)
 *  31   PA7       Video data           -- NOT AVAILABLE
 *
 * ============================================================
 * SPI / 25LC640 External EEPROM (U3)
 * ============================================================
 *  MOSI    PB5 (pin 5)
 *  MISO    PB6 (pin 6)
 *  SCK     PB7 (pin 7)
 *  /CS     PB4 (pin 4)
 *
 * ============================================================
 * Buzzer / Piezo (BZ1)
 * ============================================================
 *  OC2A = PD7 (pin 15)  -> Timer2 CTC tone generation
 *
 * ============================================================
 * Video (J4 RCA)
 * ============================================================
 *  Video  -> PA7 (pin 31)
 *  Sync   -> PD5 (pin 13)
 *
 * ============================================================
 * PS/2 Keyboard (J2)
 * ============================================================
 *  Clock  -> PB0 (pin 0)
 *  Data   -> PD0 (pin 8)
 */
#ifndef BOARD_PINS_H
#define BOARD_PINS_H

#include <avr/io.h>

/* ------------------------------------------------------------------ */
/* Piezo / Buzzer  (BZ1 via R8 and slide-switch S3)                   */
/* OC2A on PD7 - Timer2 CTC toggles this pin for tone generation      */
/* ------------------------------------------------------------------ */
#define PIEZO_DDR    DDRD
#define PIEZO_PORT   PORTD
#define PIEZO_BIT    PD7

/* ------------------------------------------------------------------ */
/* SPI / 25LC640 external EEPROM (U3)                                 */
/* Hardware SPI on PB4(CS) PB5(MOSI) PB6(MISO) PB7(SCK)             */
/* ------------------------------------------------------------------ */
#define XEEP_CS_DDR   DDRB
#define XEEP_CS_PORT  PORTB
#define XEEP_CS_BIT   PB4

#define SPI_DDR       DDRB
#define SPI_PORT      PORTB
#define SPI_MOSI      PB5
#define SPI_MISO      PB6
#define SPI_SCK       PB7

/* Convenience macros */
#define XEEP_CS_LOW()   (XEEP_CS_PORT &= ~(1<<XEEP_CS_BIT))
#define XEEP_CS_HIGH()  (XEEP_CS_PORT |=  (1<<XEEP_CS_BIT))

/* ------------------------------------------------------------------ */
/* UART1  (PD2=RXD1, PD3=TXD1)                                       */
/* ------------------------------------------------------------------ */
#define UART1_BAUD_RATE   9600UL
#define UART1_UBRR_VAL    ((F_CPU / 16 / UART1_BAUD_RATE) - 1)

/* ------------------------------------------------------------------ */
/* Video  (PA7=data via R2-470R, PD5=sync via R3-1k)                  */
/* ------------------------------------------------------------------ */
#define VIDEO_DATA_PORT   PORTA
#define VIDEO_DATA_DDR    DDRA
#define VIDEO_DATA_BIT    PA7
#define VIDEO_SYNC_PORT   PORTD
#define VIDEO_SYNC_DDR    DDRD
#define VIDEO_SYNC_BIT    PD5

/* ------------------------------------------------------------------ */
/* PS/2 Keyboard  (PB0=Clock, PD0=Data)                               */
/* ------------------------------------------------------------------ */
#define KBD_CLK_DDR   DDRB
#define KBD_CLK_PORT  PORTB
#define KBD_CLK_PIN   PINB
#define KBD_CLK_BIT   PB0

#define KBD_DATA_DDR  DDRD
#define KBD_DATA_PORT PORTD
#define KBD_DATA_PIN  PIND
#define KBD_DATA_BIT  PD0

/* ------------------------------------------------------------------ */
/* Yellow LED D3  (PD6 via R5-470R, active high)                      */
/* ------------------------------------------------------------------ */
#define LED_DDR   DDRD
#define LED_PORT  PORTD
#define LED_BIT   PD6

/* ------------------------------------------------------------------ */
/* AWRITE / DWRITE / AREAD / DREAD logical pin mapping                */
/*                                                                     */
/* MightyCore standard pinout for ATmega1284P:                         */
/*   0-7   = PB0-PB7                                                   */
/*   8-15  = PD0-PD7                                                   */
/*  16-23  = PC0-PC7                                                   */
/*  24-31  = PA0-PA7                                                   */
/*                                                                     */
/* Reserved / unavailable pins:                                        */
/*   0  = PB0  (PS/2 keyboard clock)                                   */
/*   8  = PD0  (PS/2 keyboard data)                                    */
/*  13  = PD5  (video sync)                                            */
/*  31  = PA7  (video data)                                            */
/* ------------------------------------------------------------------ */

/* Bit that tells pin_is_available() whether a pin can be used */
#define PIN_AVAIL_MASK_PB  0xFE  /* PB1-PB7 ok, PB0 reserved */
#define PIN_AVAIL_MASK_PD  0xDE  /* PD1-PD4,PD6,PD7 ok, PD0,PD5 reserved */
#define PIN_AVAIL_MASK_PC  0xFF  /* PC0-PC7 all ok */
#define PIN_AVAIL_MASK_PA  0x7F  /* PA0-PA6 ok, PA7 reserved */

/* Returns 1 if the logical pin number is usable for GPIO, 0 if reserved */
/* pin_is_available(pin): Return 1 if the MightyCore logical pin number 'pin'
 * is safe to use as a general-purpose I/O pin, 0 if it is reserved by the
 * system (keyboard, video, SPI).  Used by DREAD/DWRITE/AWRITE to validate
 * the pin argument before touching hardware. */
static inline uint8_t pin_is_available(uint8_t pin)
{
    uint8_t bit = pin & 7;
    if (pin < 8)  return (PIN_AVAIL_MASK_PB >> bit) & 1;
    if (pin < 16) return (PIN_AVAIL_MASK_PD >> bit) & 1;
    if (pin < 24) return (PIN_AVAIL_MASK_PC >> bit) & 1;
    if (pin < 32) return (PIN_AVAIL_MASK_PA >> bit) & 1;
    return 0;  /* pin >= 32: invalid */
}

/* pin_to_ddr(pin): Return a pointer to the DDR register for logical pin 'pin'.
 * Used by DWRITE/AWRITE to set the pin direction to output. */
static inline volatile uint8_t *pin_to_ddr(uint8_t pin)
{
    if (pin < 8)  return &DDRB;
    if (pin < 16) return &DDRD;
    if (pin < 24) return &DDRC;
    return &DDRA;
}

/* pin_to_port(pin): Return a pointer to the PORT register for logical pin 'pin'.
 * Used by DWRITE/AWRITE to drive the output level. */
static inline volatile uint8_t *pin_to_port(uint8_t pin)
{
    if (pin < 8)  return &PORTB;
    if (pin < 16) return &PORTD;
    if (pin < 24) return &PORTC;
    return &PORTA;
}

/* pin_to_pin(pin): Return a pointer to the PIN (input) register for logical pin
 * 'pin'.  Used by DREAD to sample the digital input level. */
static inline volatile uint8_t *pin_to_pin(uint8_t pin)
{
    if (pin < 8)  return &PINB;
    if (pin < 16) return &PIND;
    if (pin < 24) return &PINC;
    return &PINA;
}

/* pin_to_bit(pin): Return the bit number (0-7) within the port registers for
 * logical pin 'pin'.  The bit is always pin & 7 regardless of port. */
static inline uint8_t pin_to_bit(uint8_t pin) { return pin & 7; }

#endif /* BOARD_PINS_H */

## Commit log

2024-03-07 Schematics and PCB design files added
2024-03-27 Forked TinyBasic Plus v0.18 including libraries
2024-04-03 PCB Version v1.1 - AV Video RCA Jack polarity reversed, silkscreen updates
2024-04-04 Serial Boomerang Shield schematic + PCB added
2024-04-04 Serial Boomerang Shield updated + Gerber files generated
2024-04-05 Serial Boomerang Shield updated, power output header added
2024-04-05 AVR-SBC board updated - USBasp header realigned to match 0.254mm grid
2024-04-05 AVR-SBC board updated - Power header realigned to match 0.254mm grid
2024-04-05 Serial Boomerang Shield updated - Power header realigned to match 0.254mm grid
2024-04-05 AVR-SBC board updated - GPIO headers and IC-s realigned to match 0.254mm grid
2024-04-05 Serial Boomerang Shield updated - GPIO headers realigned to match 0.254mm grid
2024-04-05 AVR-SBC board updated - Silkscreen updates and fill zones updated to match 1mm grid
2024-04-05 Serial Boomerang Shield schematic PDF added
2024-04-05 AVR-SBC board updated - Mounting holes aligned to match 1mm grid
2024-04-06 Serial commands added, with fixed 9600 baud: SERCOM, SERLOAD, SERIN
2024-04-07 SERCOM and SERIN renamed to SERPRINT and SERREAD
2024-04-07 SEROPEN and SERCLOSE commands added to be able to close the serial port and use the RX/TX pins as GPIO
2024-04-07 INCHRN command added - same as INPUT but doesnt wait for Return
2024-04-07 XPOKE and XPEEK made compatible with 25LC640 (byte address replaced with int)
2024-04-09 AVR-SBC board updated: Connectors moved closer to each other to leave space for shields
2024-04-09 AVR-SBC board updated: Silkscreen version number updated
2024-04-16 AVR-SBC board updated: Silkscreen updated
2024-05-01 THEN syntax check added after IF command to have complete IF...THEN... structure
2024-05-01 SBC Studio v1.0 code added - programming IDE and code text editor for the AVR-SBC
2024-05-01 SBC Studio bugfix: Context menu binding was for the first tab only, now it is working for all tabs
2024-05-01 SBC Studio bugfix: Context menu Select All option binding fixed
2024-05-02 SBC Studio updated: COM ports now appear sorted in menu
2024-05-02 SBC Studio updated: Program menu extended with Stop programming and Send test string options
2024-05-03 AVR-SBC code updated: SERREAD length limit removed
2024-05-03 AVR-SBC code updated: SERREAD prints only human-readable ASCII characters
2024-05-03 AVR-SBC code updated: SERREAD Timeout of 1 second introduced to prevent blocking
2024-05-04 PC tools added: Bitmap Loader, MIDI to BAS converter + example outputs added for PC tools
2024-05-04 BASIC example programs added to examples folder: BlinkLED, MazeGame, PianoKeyboard, SevenSegment, etc.
2024-05-04 AVR-SBC code updated: Print statements updated
2024-05-05 Empty boomerang shield template added as a base to develop projects on
2024-05-05 AVR-SBC board schematic rearranged to make it look nicer, PDF regenerated
2024-05-05 Schematic folder: gitignore updated
2024-05-05 KiCad gitignore added to boomerang shields
2024-05-05 docs updated: AVR-SBC logo added
2024-05-05 docs updated: AVR-SBC mainboard photo added
2024-05-05 PC tools updated: Bitmap loader icons updated
2025-11-20 Mainboard top view photo added
2026-03-05 Schematic: Update to v1.3, schottky diode added to ISP header for protection, decoupling capacitors added
2026-03-18 PCB updated
2026-03-26 PCB reverted to release version v1.2
2026-03-29 AVR-SBC source code ported to bare-metal AVR C with custom graphics library
2026-03-29 Removed unused libraries
2026-03-29 Screenshots added to docs/images
2026-03-29 Additional photos added to docs/images
2026-03-29 Schematic migrated to KiCad 9, image added to docs/images
2026-03-29 Screenshots moved
2026-03-30 Set US/English QWERTY as default keyboard layout in Makefile and in keyboard.h instead of Hungarian QWERTZ
2026-03-30 Optional THEN keyword added to IF in BASIC interpreter
2026-03-30 SBC Studio v1.1.0 release
2026-03-30 SBC Studio screenshot added to docs/images
2026-03-30 BASIC example programs updated
